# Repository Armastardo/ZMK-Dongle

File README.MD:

# ZMK Dongle

## Warning! WIP

### Parts list:
- m2 3.5 inserts - https://www.aliexpress.com/item/1005003582355741.html
- any m2 screws (5mm should work)
- jst ph 2 pin smd connector for battery - https://www.aliexpress.com/item/1005002469884046.html
- switch (6mm) https://www.aliexpress.com/item/10000056364450.html https://www.aliexpress.com/item/1005005544512054.html
- button (6x6x10)

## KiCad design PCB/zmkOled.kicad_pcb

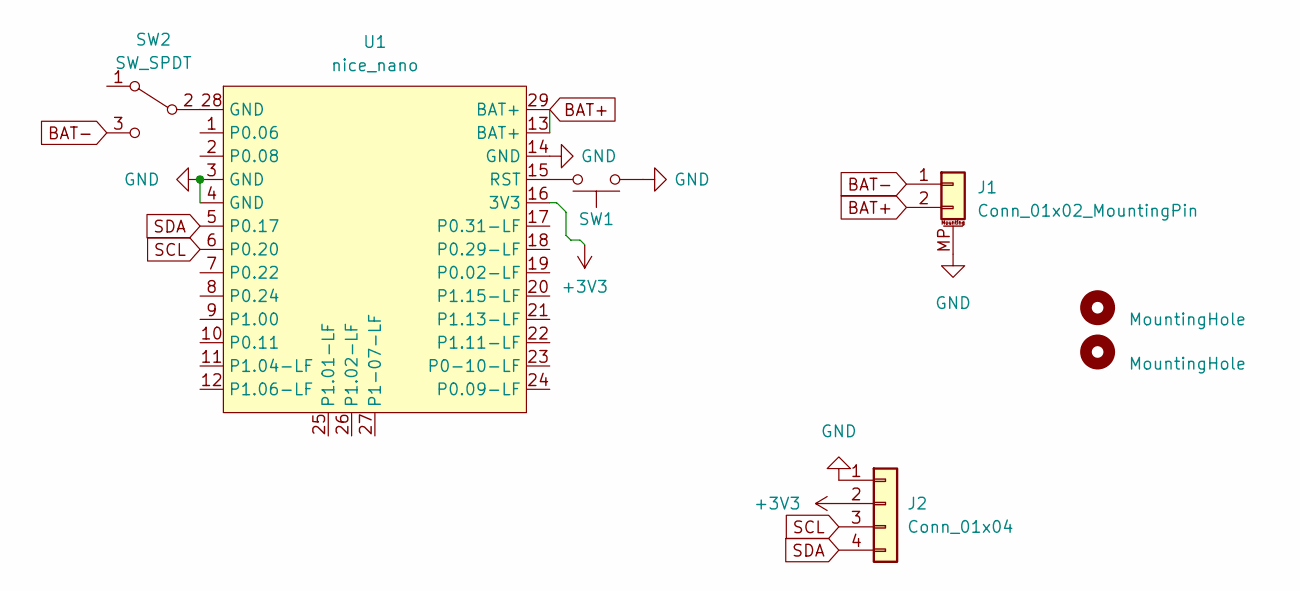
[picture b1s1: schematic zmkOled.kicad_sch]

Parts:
H1, H2: MountingHole; MountingHole_2.2mm_M2
J1: Conn_01x02_MountingPin; JST_PH_S2B-PH-SM4-TB_1x02-1MP_P2.00mm_Horizontal
J2: Conn_01x04; PinHeader_1x04_P2.54mm_Vertical
SW1: SW_Push; SW_Tactile_SPST_Angled_PTS645Vx83-2LFS
SW2: SW_SPDT; SW_CuK_OS102011MA1QN1_SPDT_Angled
U1: nice_nano; nice_nano_AH_USBup

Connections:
+3V3: J2.2, U1.16 (3V3)
BAT+: J1.2, U1.13 (BAT+), U1.29 (BAT+)
BAT-: J1.1, SW2.3 (C)
GND: J1.MP (MountPin), J2.1, SW1.1, U1.3 (GND), U1.4 (GND), U1.14 (GND)
unnamed: SW2.2 (B), U1.28 (GND)
unnamed: SW1.2, U1.15 (RST)
SCL: J2.3, U1.6 (P0.20)
SDA: J2.4, U1.5 (P0.17)

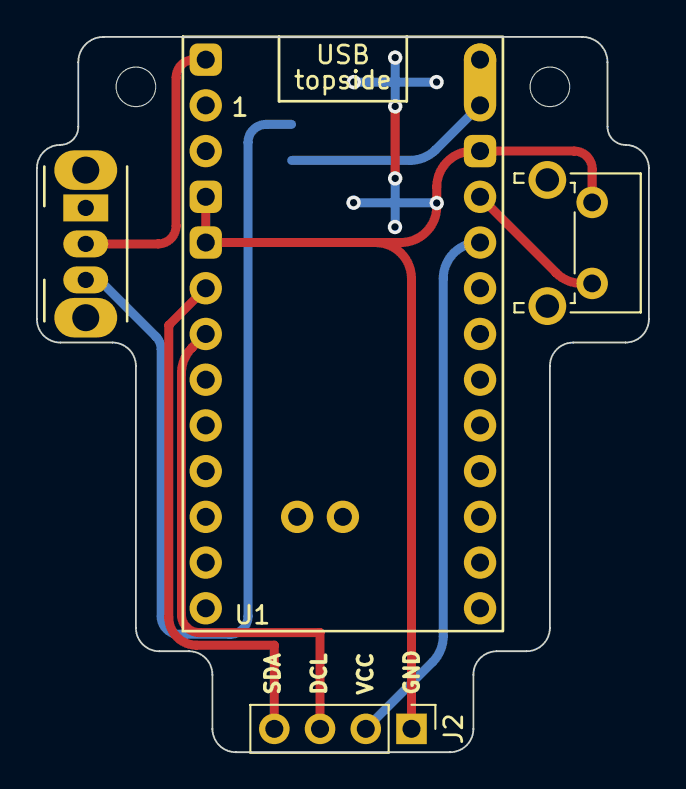
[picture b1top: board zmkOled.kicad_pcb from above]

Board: 2 copper layers, 34.0 x 39.7 mm, 7 parts (1 on the bottom side), 8 nets.

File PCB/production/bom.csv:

Designator,Footprint,Quantity,Value,LCSC Part #
J1,JST_PH_S2B-PH-SM4-TB_1x02-1MP_P2.00mm_Horizontal,1,Conn_01x02_MountingPin,
J2,PinHeader_1x04_P2.54mm_Vertical,1,Conn_01x04,
SW1,SW_Tactile_SPST_Angled_PTS645Vx83-2LFS,1,SW_Push,
SW2,SW_CuK_OS102011MA1QN1_SPDT_Angled,1,SW_SPDT,
